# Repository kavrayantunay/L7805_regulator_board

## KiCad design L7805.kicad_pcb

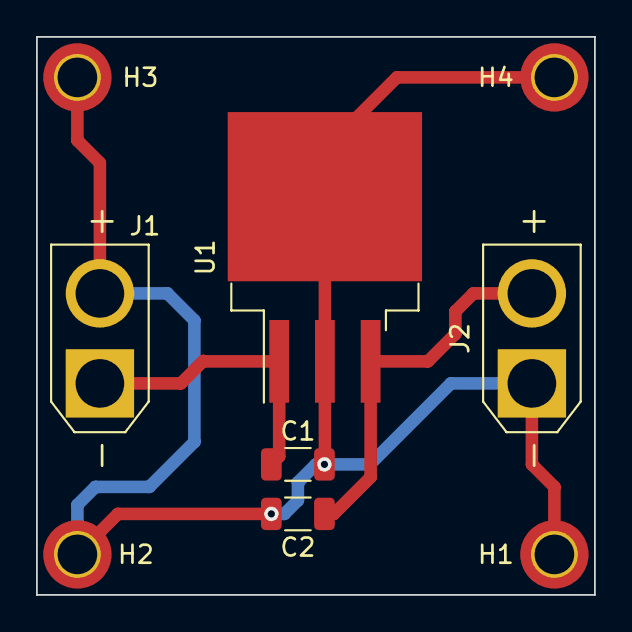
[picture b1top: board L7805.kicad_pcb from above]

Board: 2 copper layers, 31.0 x 31.0 mm, 9 parts (0 on the bottom side), 3 nets.

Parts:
C1: 330nF; C_1206_3216Metric
C2: 0.1uF; C_1206_3216Metric
H1, H2, H3, H4: MountingHole_Pad; MountingHole_2.2mm_M2_DIN965_Pad_TopBottom
J1, J2: Conn_01x02_Male; AMASS_XT30U-M_1x02_P5.0mm_Vertical
U1: L7805; TO-263-3_TabPin2

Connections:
GND: C1.2, C2.2, H1.1, H2.1, H3.1, H4.1, J1.2, J2.1, U1.2 (GND)
unnamed: C1.1, J1.1, U1.1 (IN)
unnamed: C2.1, J2.2, U1.3 (OUT)
